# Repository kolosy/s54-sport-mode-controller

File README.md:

# S54 Sport mode controller
This is a sport mode controller for the S54 Z3 M. It works by pulling a line to the DME to ground for 1 second, and then keeping track of state and turning on the dash light. This only works on the S54 engined Z3 M, as the functoinality exists in the DME but isn't broken out by default. You will need to add the dash light, and the missing pin housing to the DME connector to make this work.

The housing STLs were made with OnShape, and are available as CAD files here:
https://cad.onshape.com/documents/bd9cbe37f7debc0799cd37cb/w/cd3ee4e9e2b90868aebbf150/e/c24e36f81ab31e6954b87d38

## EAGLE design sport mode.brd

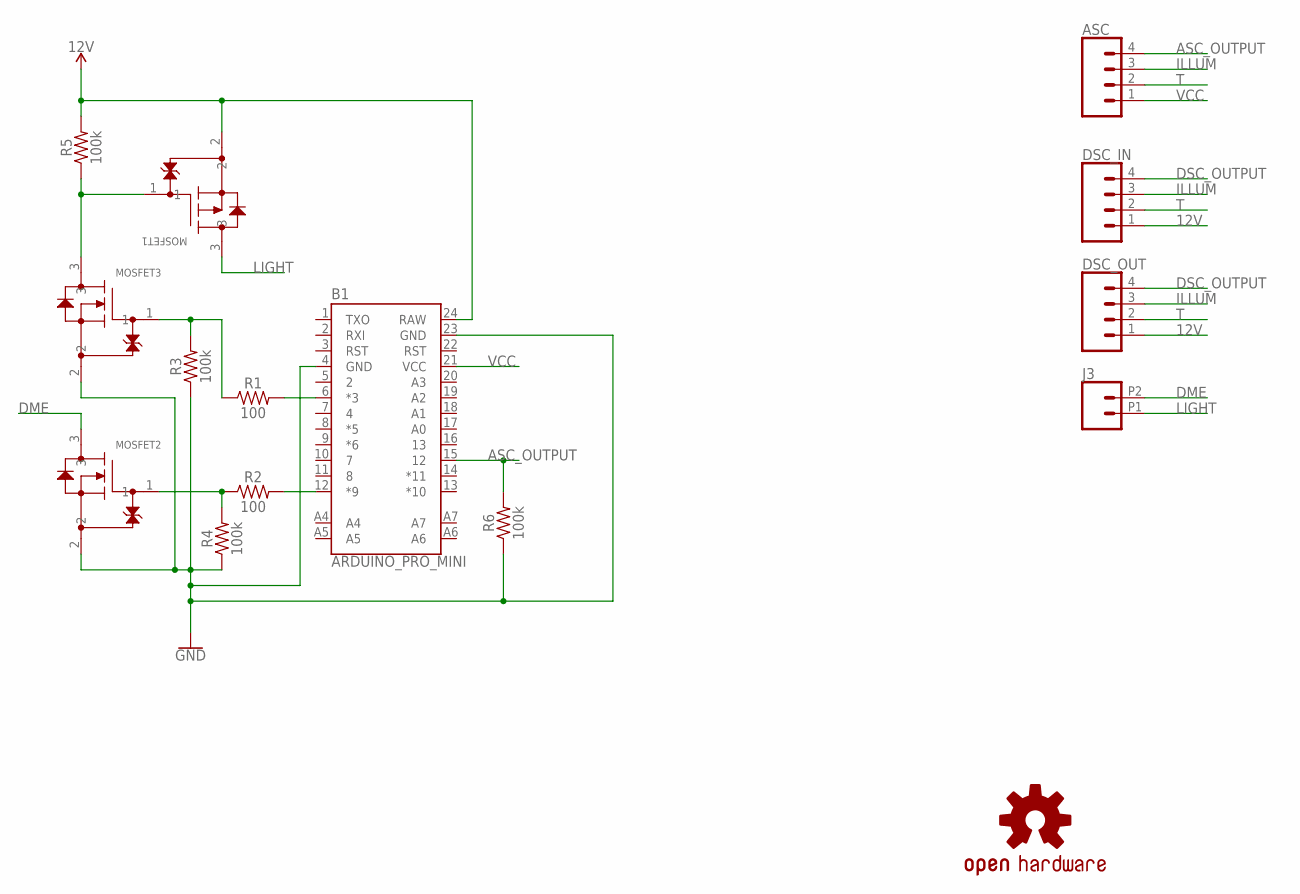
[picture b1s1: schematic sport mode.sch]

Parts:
ASC: CONN_04; 1X04
B1: ARDUINO_PRO_MINI
DSC_IN: CONN_04; 1X04
DSC_OUT: CONN_04; 1X04
J3: CONN_022.54MM_SCREWTERM; 1X02_2.54_SCREWTERM
LOGO1: OSHW-LOGOL-COPPER; OSHW-LOGO-L_COPPER
MOSFET1: SSM3J328R; SOT-23F
MOSFET2, MOSFET3: SSM3K329R; SOT-23F
R1, R2: 100; 0603
R3, R4, R5, R6: 100k; 0603

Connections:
12V: B1.24 (RAW), DSC_IN.1, DSC_OUT.1, MOSFET1.2, R5.2
ASC_OUTPUT: ASC.4, B1.15 (12), R6.2
DME: J3.P2 (2), MOSFET2.3
DSC_OUTPUT: DSC_IN.4, DSC_OUT.4
ILLUM: ASC.3, DSC_IN.3, DSC_OUT.3
LIGHT: J3.P1 (1), MOSFET1.3
unnamed: B1.12 (*9), R2.2
unnamed: B1.6 (*3), R1.2
unnamed: MOSFET2.1, R2.1, R4.2
unnamed: MOSFET3.1, R1.1, R3.2
unnamed: MOSFET1.1, MOSFET3.3, R5.1
T: ASC.2, B1.4 (GND), B1.23 (GND), DSC_IN.2, DSC_OUT.2, MOSFET2.2, MOSFET3.2, R3.1, R4.1, R6.1
VCC: ASC.1, B1.21 (VCC)

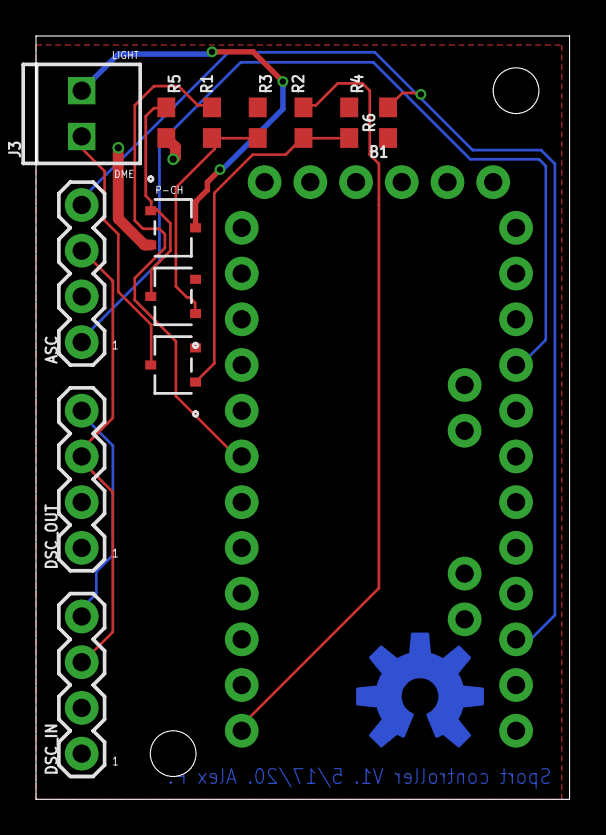
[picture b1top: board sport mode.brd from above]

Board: 2 copper layers, 29.6 x 42.4 mm, 15 parts (1 on the bottom side), 13 nets.

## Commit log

2020-06-03 Create LICENSE

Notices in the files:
parts and their libraries:
SparkFun-Connectors: Licensing: Creative Commons ShareAlike 4.0 International - https://creativecommons.org/licenses/by-sa/4.0
